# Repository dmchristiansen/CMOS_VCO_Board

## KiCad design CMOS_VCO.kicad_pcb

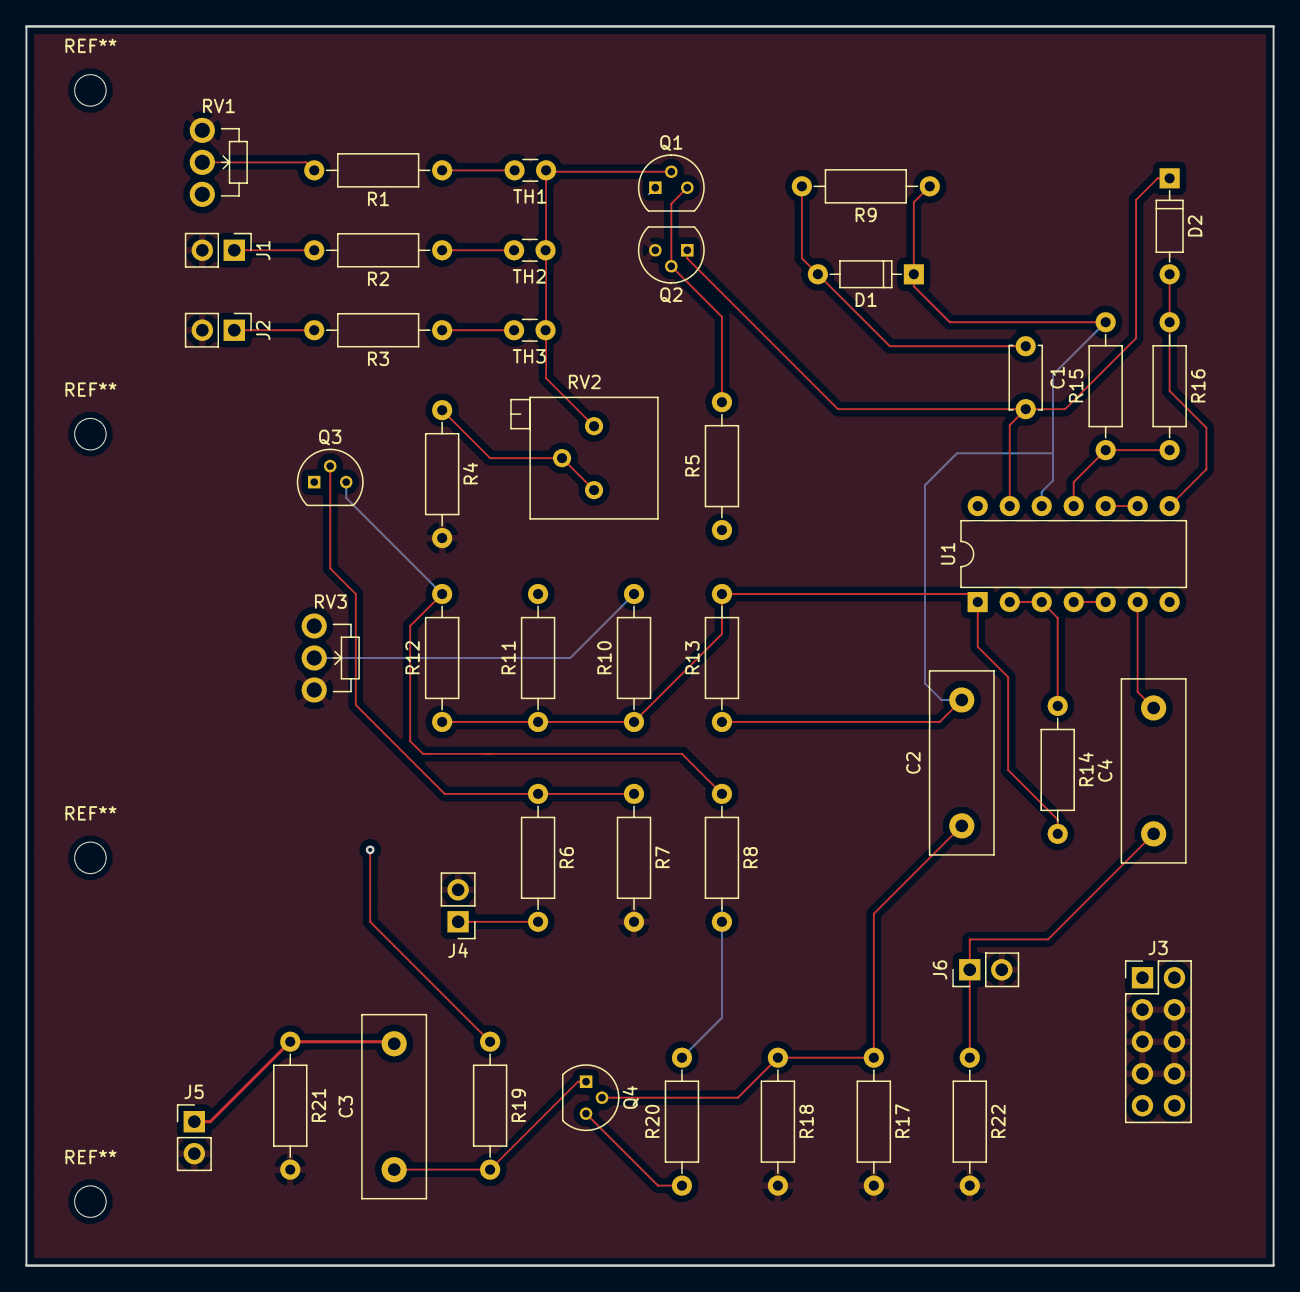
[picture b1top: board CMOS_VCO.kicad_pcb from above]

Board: 2 copper layers, 99.1 x 98.4 mm, 45 parts (0 on the bottom side), 31 nets.

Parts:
C1: 2.2nF; C_Disc_D5.0mm_W2.5mm_P5.00mm
C2, C3, C4: 220nF; C_Disc_D14.5mm_W5.0mm_P10.00mm
D1, D2: 1N4148; D_DO-35_SOD27_P7.62mm_Horizontal
J1: CV 1; Pin_Header_Straight_1x02_Pitch2.54mm
J2: CV 2; Pin_Header_Straight_1x02_Pitch2.54mm
J3: Power header; Pin_Header_Straight_2x05_Pitch2.54mm
J4: PWM; Pin_Header_Straight_1x02_Pitch2.54mm
J5: saw out; Pin_Header_Straight_1x02_Pitch2.54mm
J6: pulse out; Pin_Header_Straight_1x02_Pitch2.54mm
Q1: BC560; TO-92_Molded_Narrow
Q2, Q3, Q4: BC548; TO-92_Molded_Narrow
R1, R2, R3, R6, R10, R12, R14, R17, R21, R22: 100k; R_Axial_DIN0207_L6.3mm_D2.5mm_P10.16mm_Horizontal
R4: 1.5k; R_Axial_DIN0207_L6.3mm_D2.5mm_P10.16mm_Horizontal
R5, R7: 1M; R_Axial_DIN0207_L6.3mm_D2.5mm_P10.16mm_Horizontal
R8, R15: 10k; R_Axial_DIN0207_L6.3mm_D2.5mm_P10.16mm_Horizontal
R9: 680; R_Axial_DIN0207_L6.3mm_D2.5mm_P10.16mm_Horizontal
R11: 68k; R_Axial_DIN0207_L6.3mm_D2.5mm_P10.16mm_Horizontal
R13: 47k; R_Axial_DIN0207_L6.3mm_D2.5mm_P10.16mm_Horizontal
R16: 22k; R_Axial_DIN0207_L6.3mm_D2.5mm_P10.16mm_Horizontal
R18: 33k; R_Axial_DIN0207_L6.3mm_D2.5mm_P10.16mm_Horizontal
R19: 3.3k; R_Axial_DIN0207_L6.3mm_D2.5mm_P10.16mm_Horizontal
R20: 1k; R_Axial_DIN0207_L6.3mm_D2.5mm_P10.16mm_Horizontal
RV1, RV3: 22k; Potentiometer_WirePads_Small
RV2: 1k; Potentiometer_Trimmer_Bourns_3299P
TH1, TH2, TH3: 10k; C_Disc_D3.0mm_W1.6mm_P2.50mm
U1: 4069; DIP-14_W7.62mm

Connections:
+12V: J3.1, J3.2, Q3.1, R5.1, R11.2, R19.1, RV3.1
-12V: J3.9, J3.10, Q1.1, R8.2, R20.2, RV1.3
GND: J1.2, J2.2, J3.3, J3.4, J3.5, J3.6, J3.7, J3.8, J4.2, J5.2, J6.2, Q2.3, R4.2, R7.2, R17.2, R18.2, R21.2, R22.2, RV1.1, RV3.3
unnamed: C1.1, D1.2, R9.2
unnamed: C1.2, D2.1, Q2.1, U1.13
unnamed: C2.1, Q4.2, R17.1, R18.1
unnamed: C2.2, D1.1, R9.1, R13.1, R15.2, U1.12
unnamed: C3.1, Q4.1, R19.2
unnamed: C3.2, J5.1, R21.1
unnamed: C4.1, J6.1, R22.1
unnamed: C4.2, U1.6
unnamed: D2.2, R16.1, U1.8
unnamed: J1.1, R2.2
unnamed: J2.1, R3.2
unnamed: J4.1, R6.2
unnamed: Q1.2, RV2.1, TH1.1, TH2.1, TH3.1
unnamed: Q1.3, Q2.2, R5.2
unnamed: Q3.2, R6.1, R7.1
unnamed: Q3.3, R8.1, R12.2
unnamed: Q4.3, R20.1
unnamed: R1.1, TH1.2
unnamed: R1.2, RV1.2
unnamed: R2.1, TH2.2
unnamed: R3.1, TH3.2
unnamed: R4.1, RV2.2, RV2.3
unnamed: R10.1, R11.1, R12.1, R13.2, R14.2, U1.1
unnamed: R10.2, RV3.2
unnamed: R14.1, U1.2, U1.3
unnamed: R15.1, R16.2, U1.11
unnamed: U1.4, U1.5
unnamed: U1.9, U1.10

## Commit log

2018-08-09 added files
2018-11-02 added faceplate drill template
2018-11-02 fixed drill tremplate scale
2018-11-02 stuff
